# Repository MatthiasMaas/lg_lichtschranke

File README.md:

# lg_photogate

Photogates for education are expensive. This one ist not.

## Circuit

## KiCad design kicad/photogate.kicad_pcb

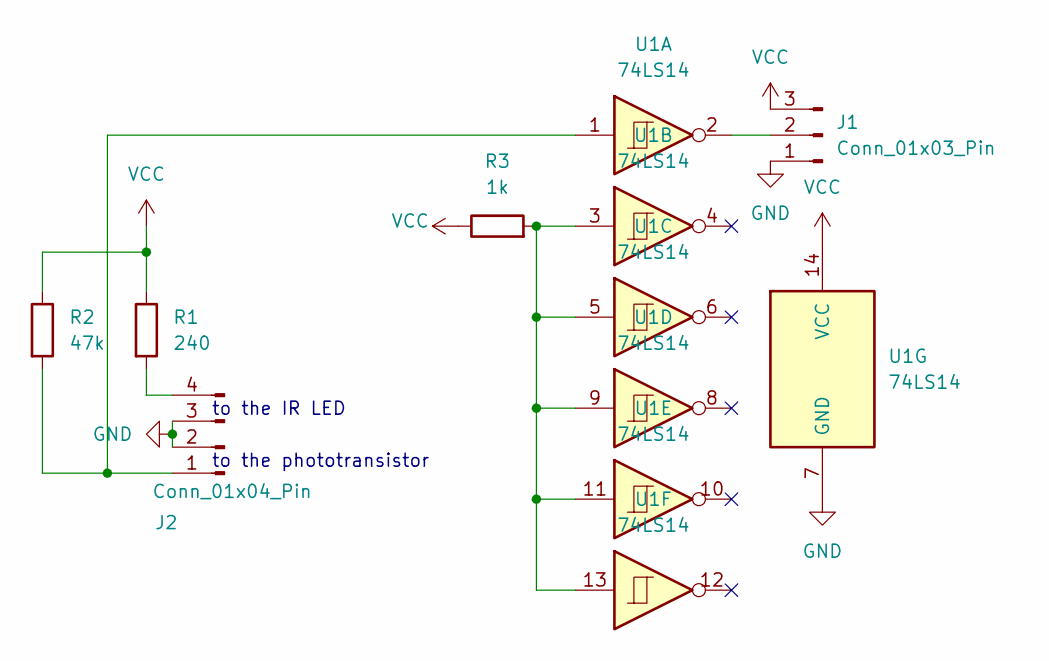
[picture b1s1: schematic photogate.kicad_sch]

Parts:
J1: Conn_01x03_Pin; SolderWire-0.5sqmm_1x03_P4.6mm_D0.9mm_OD2.1mm
J2: Conn_01x04_Pin; SolderWire-0.75sqmm_1x04_P4.8mm_D1.25mm_OD2.3mm
R1: 240; R_Axial_DIN0207_L6.3mm_D2.5mm_P10.16mm_Horizontal
R2: 47k; R_Axial_DIN0207_L6.3mm_D2.5mm_P10.16mm_Horizontal
R3: 1k; R_Axial_DIN0207_L6.3mm_D2.5mm_P10.16mm_Horizontal
U1: 74LS14; DIP-14_W7.62mm_Socket

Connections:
GND: J1.1, J2.2, J2.3, U1.7 (GND)
unnamed: J1.2, U1.2
unnamed: J2.1, R2.2, U1.1
unnamed: J2.4, R1.2
unnamed: R3.2, U1.3, U1.5, U1.9, U1.11, U1.13
VCC: J1.3, R1.1, R2.1, R3.1, U1.14 (VCC)

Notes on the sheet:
to the phototransistor
to the IR LED

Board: 2 copper layers, 6 parts (0 on the bottom side), 6 nets, no tracks yet.

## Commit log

2025-07-21 avr sources initial
2025-07-21 added freecad files
2025-07-23 picture of the circuit for documentatation
2025-07-23 circuit added
2025-07-23 Update README.md with circuit
2025-07-28 update of doc; school intern docs
2025-07-28 doc changed
2025-07-28 photos of the open photogate and the breakoutboard
2025-07-28 STL exports added
2025-07-28 STL export errors corrected in clamp parts
